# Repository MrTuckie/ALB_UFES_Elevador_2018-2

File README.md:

# Elevador-UFES-2018-2
Melhorias na placa e na documentação

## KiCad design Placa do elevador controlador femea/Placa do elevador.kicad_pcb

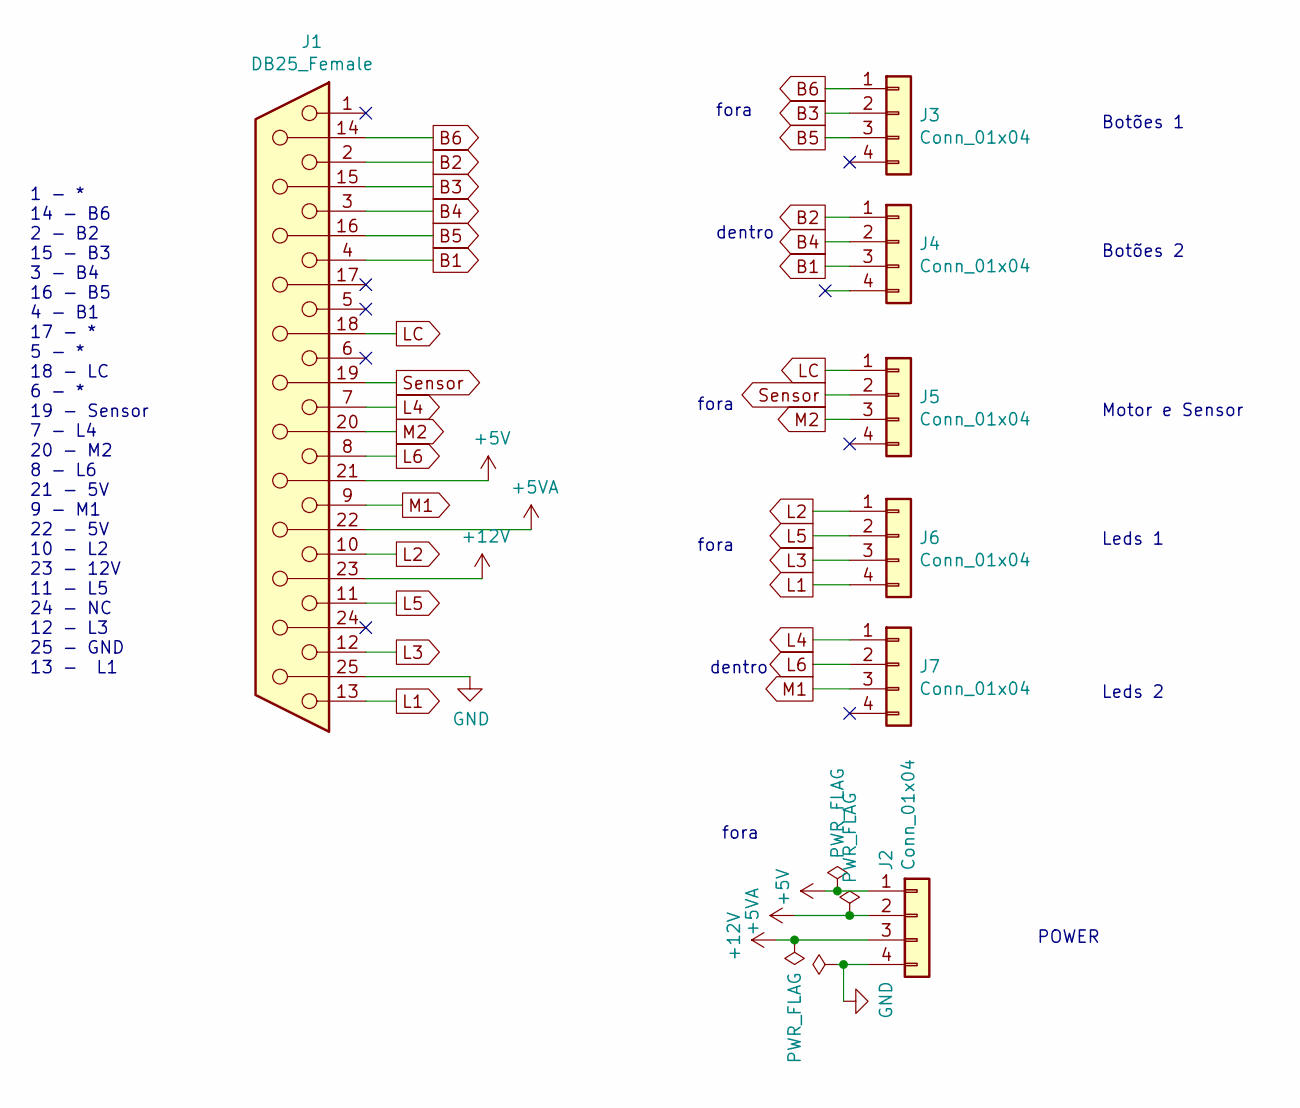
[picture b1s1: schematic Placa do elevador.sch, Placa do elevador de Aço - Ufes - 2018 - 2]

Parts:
J1: DB25_Female; DSUB-25_Female_Horizontal_P2.77x2.84mm_EdgePinOffset14.56mm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
J2, J3, J4, J5, J6, J7: Conn_01x04; PinSocket_1x04_P2.00mm_Vertical

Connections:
+5V: J1.21, J2.1
+5VA: J1.22, J2.2
+12V: J1.23, J2.3
B1: J1.4, J4.3
B2: J1.2, J4.1
B3: J1.15, J3.2
B4: J1.3, J4.2
B5: J1.16, J3.3
B6: J1.14, J3.1
GND: J1.25, J2.4
L1: J1.13, J6.4
L2: J1.10, J6.1
L3: J1.12, J6.3
L4: J1.7, J7.1
L5: J1.11, J6.2
L6: J1.8, J7.2
LC: J1.18, J5.1
M1: J1.9, J7.3
M2: J1.20, J5.3
Sensor: J1.19, J5.2

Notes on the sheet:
1 - * 14 - B6 2 - B2 15 - B3 3 - B4 16 - B5 4 - B1 17 - * 5 - * 18 - LC 6 - * 19 - Sensor 7 - L4 20 - M2 8 - L6 21 - 5V 9 - M1 22 - 5V 10 - L2 23 - 12V 11 - L5 24 - NC 12 - L3 25 - GND 13 - L1
Botões 1
Botões 2
Motor e Sensor
POWER
Leds 1
Leds 2
fora
dentro

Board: 2 copper layers, 7 parts (0 on the bottom side), 20 nets, no tracks yet.

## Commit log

2018-10-14 commit inicial
2018-10-24 Mudando de nome e atualizando os perfis
2018-11-08 Adicionando parafusos
2018-11-09 resolvendo o inferno astral de pdfs
    plot -> ps -> force a4 output -> plot -> gimp -> multiply -> save -> print -> xD
